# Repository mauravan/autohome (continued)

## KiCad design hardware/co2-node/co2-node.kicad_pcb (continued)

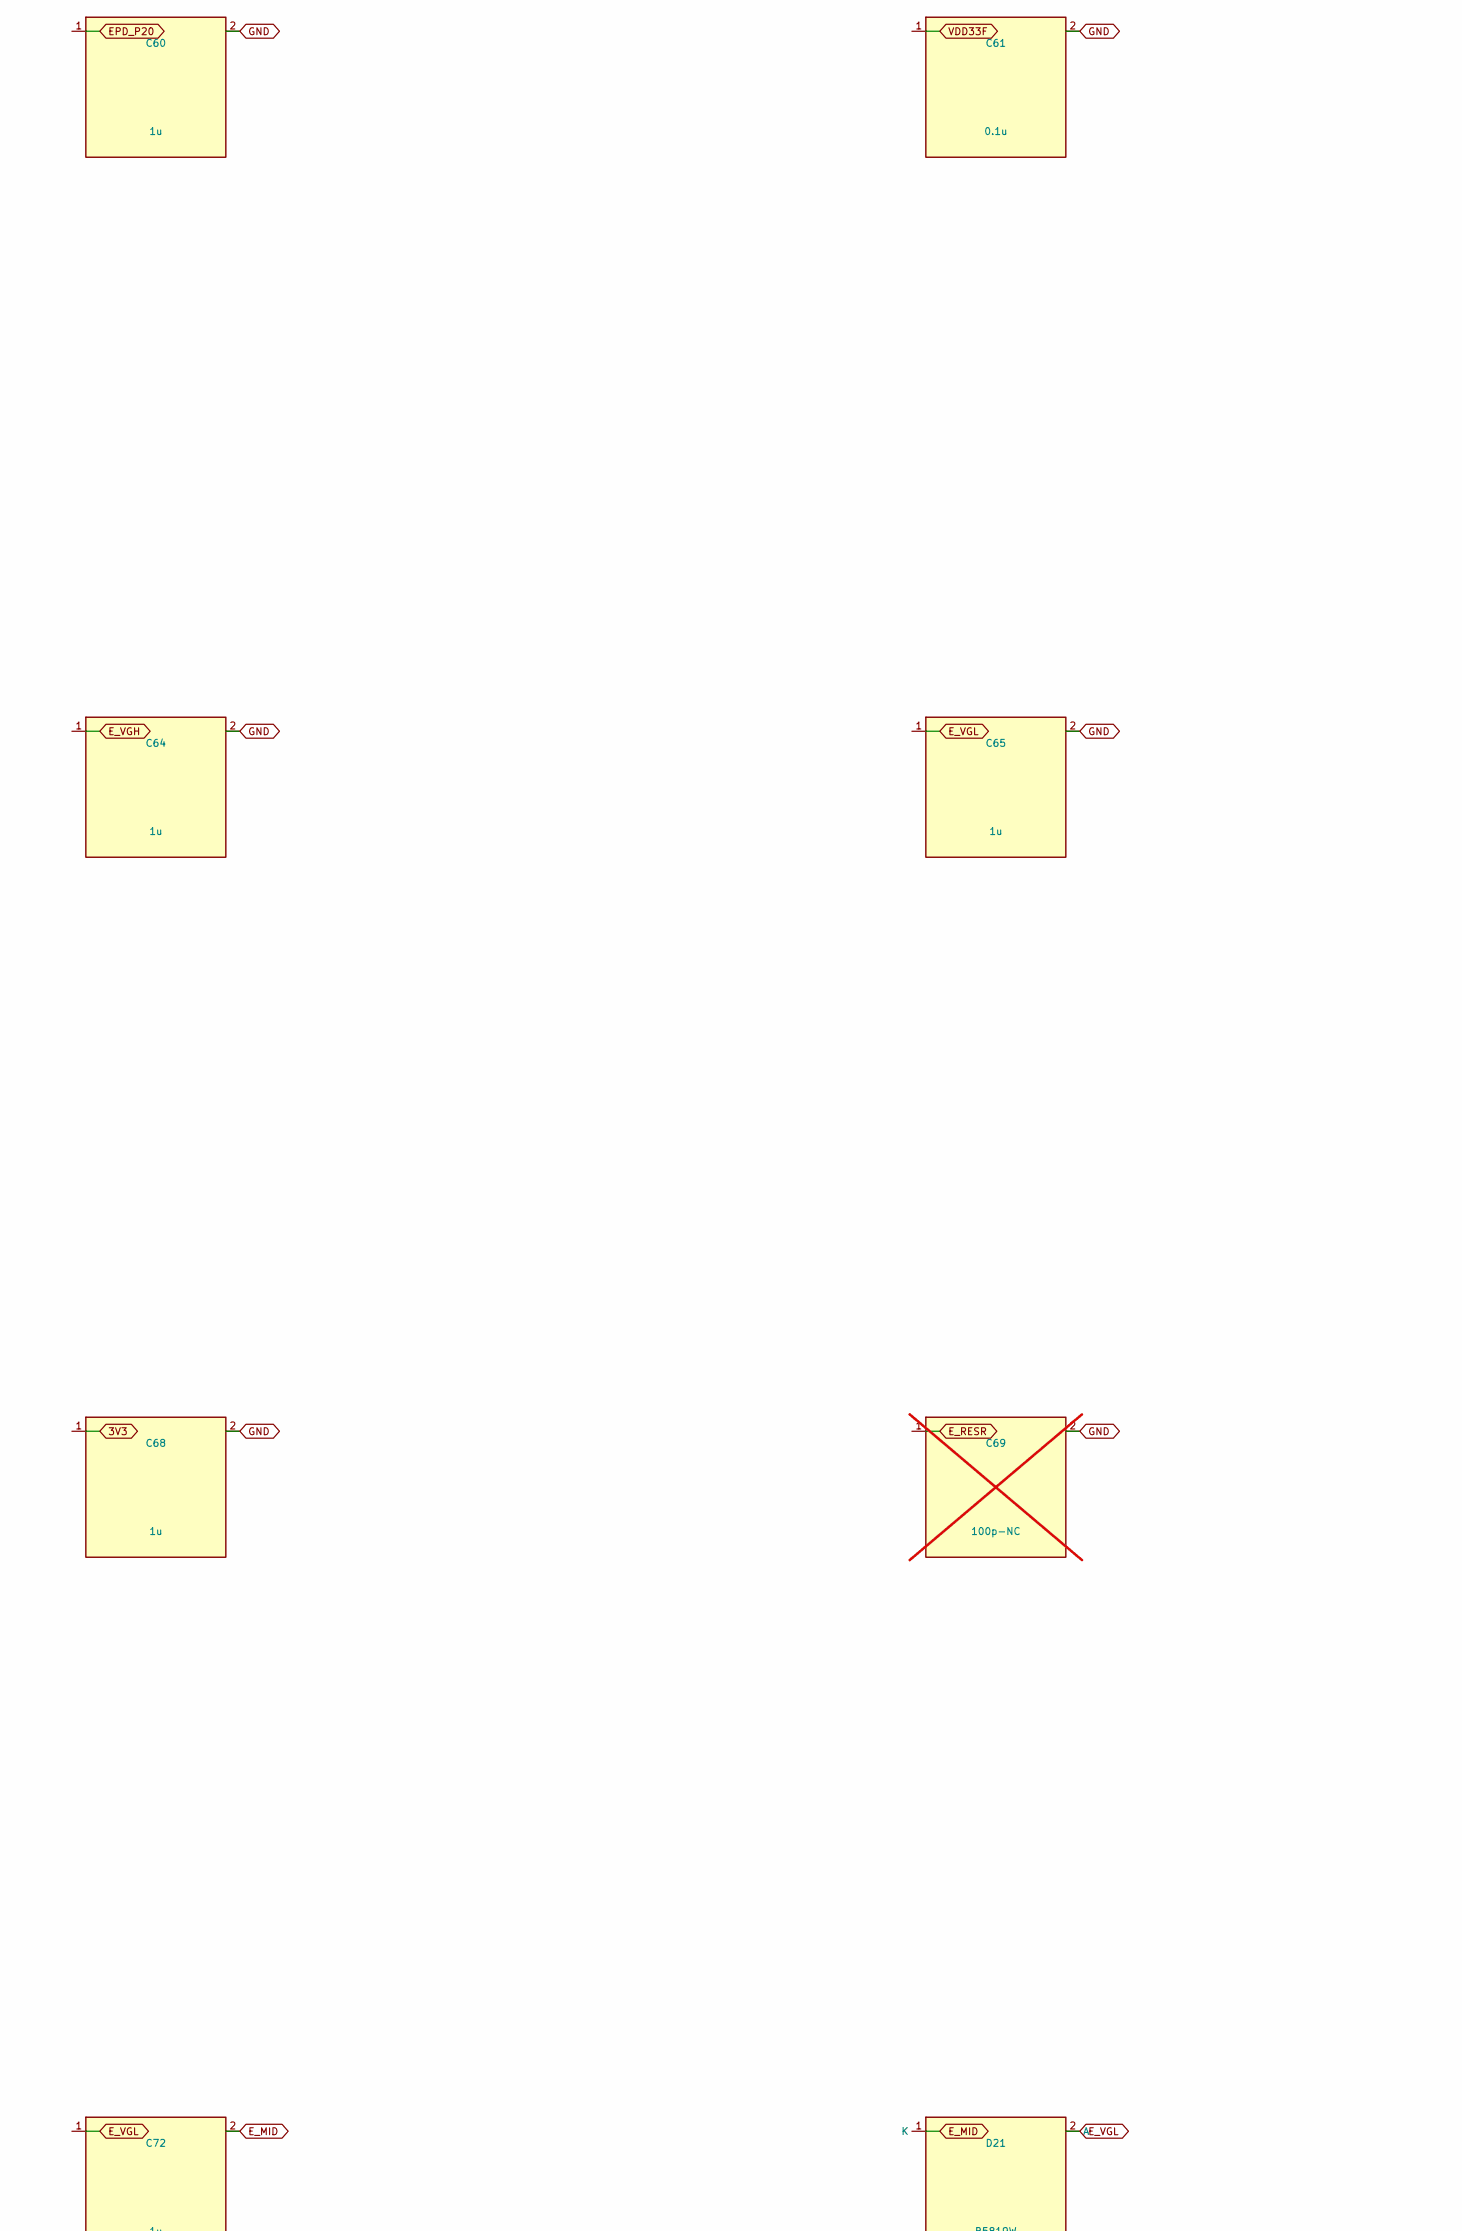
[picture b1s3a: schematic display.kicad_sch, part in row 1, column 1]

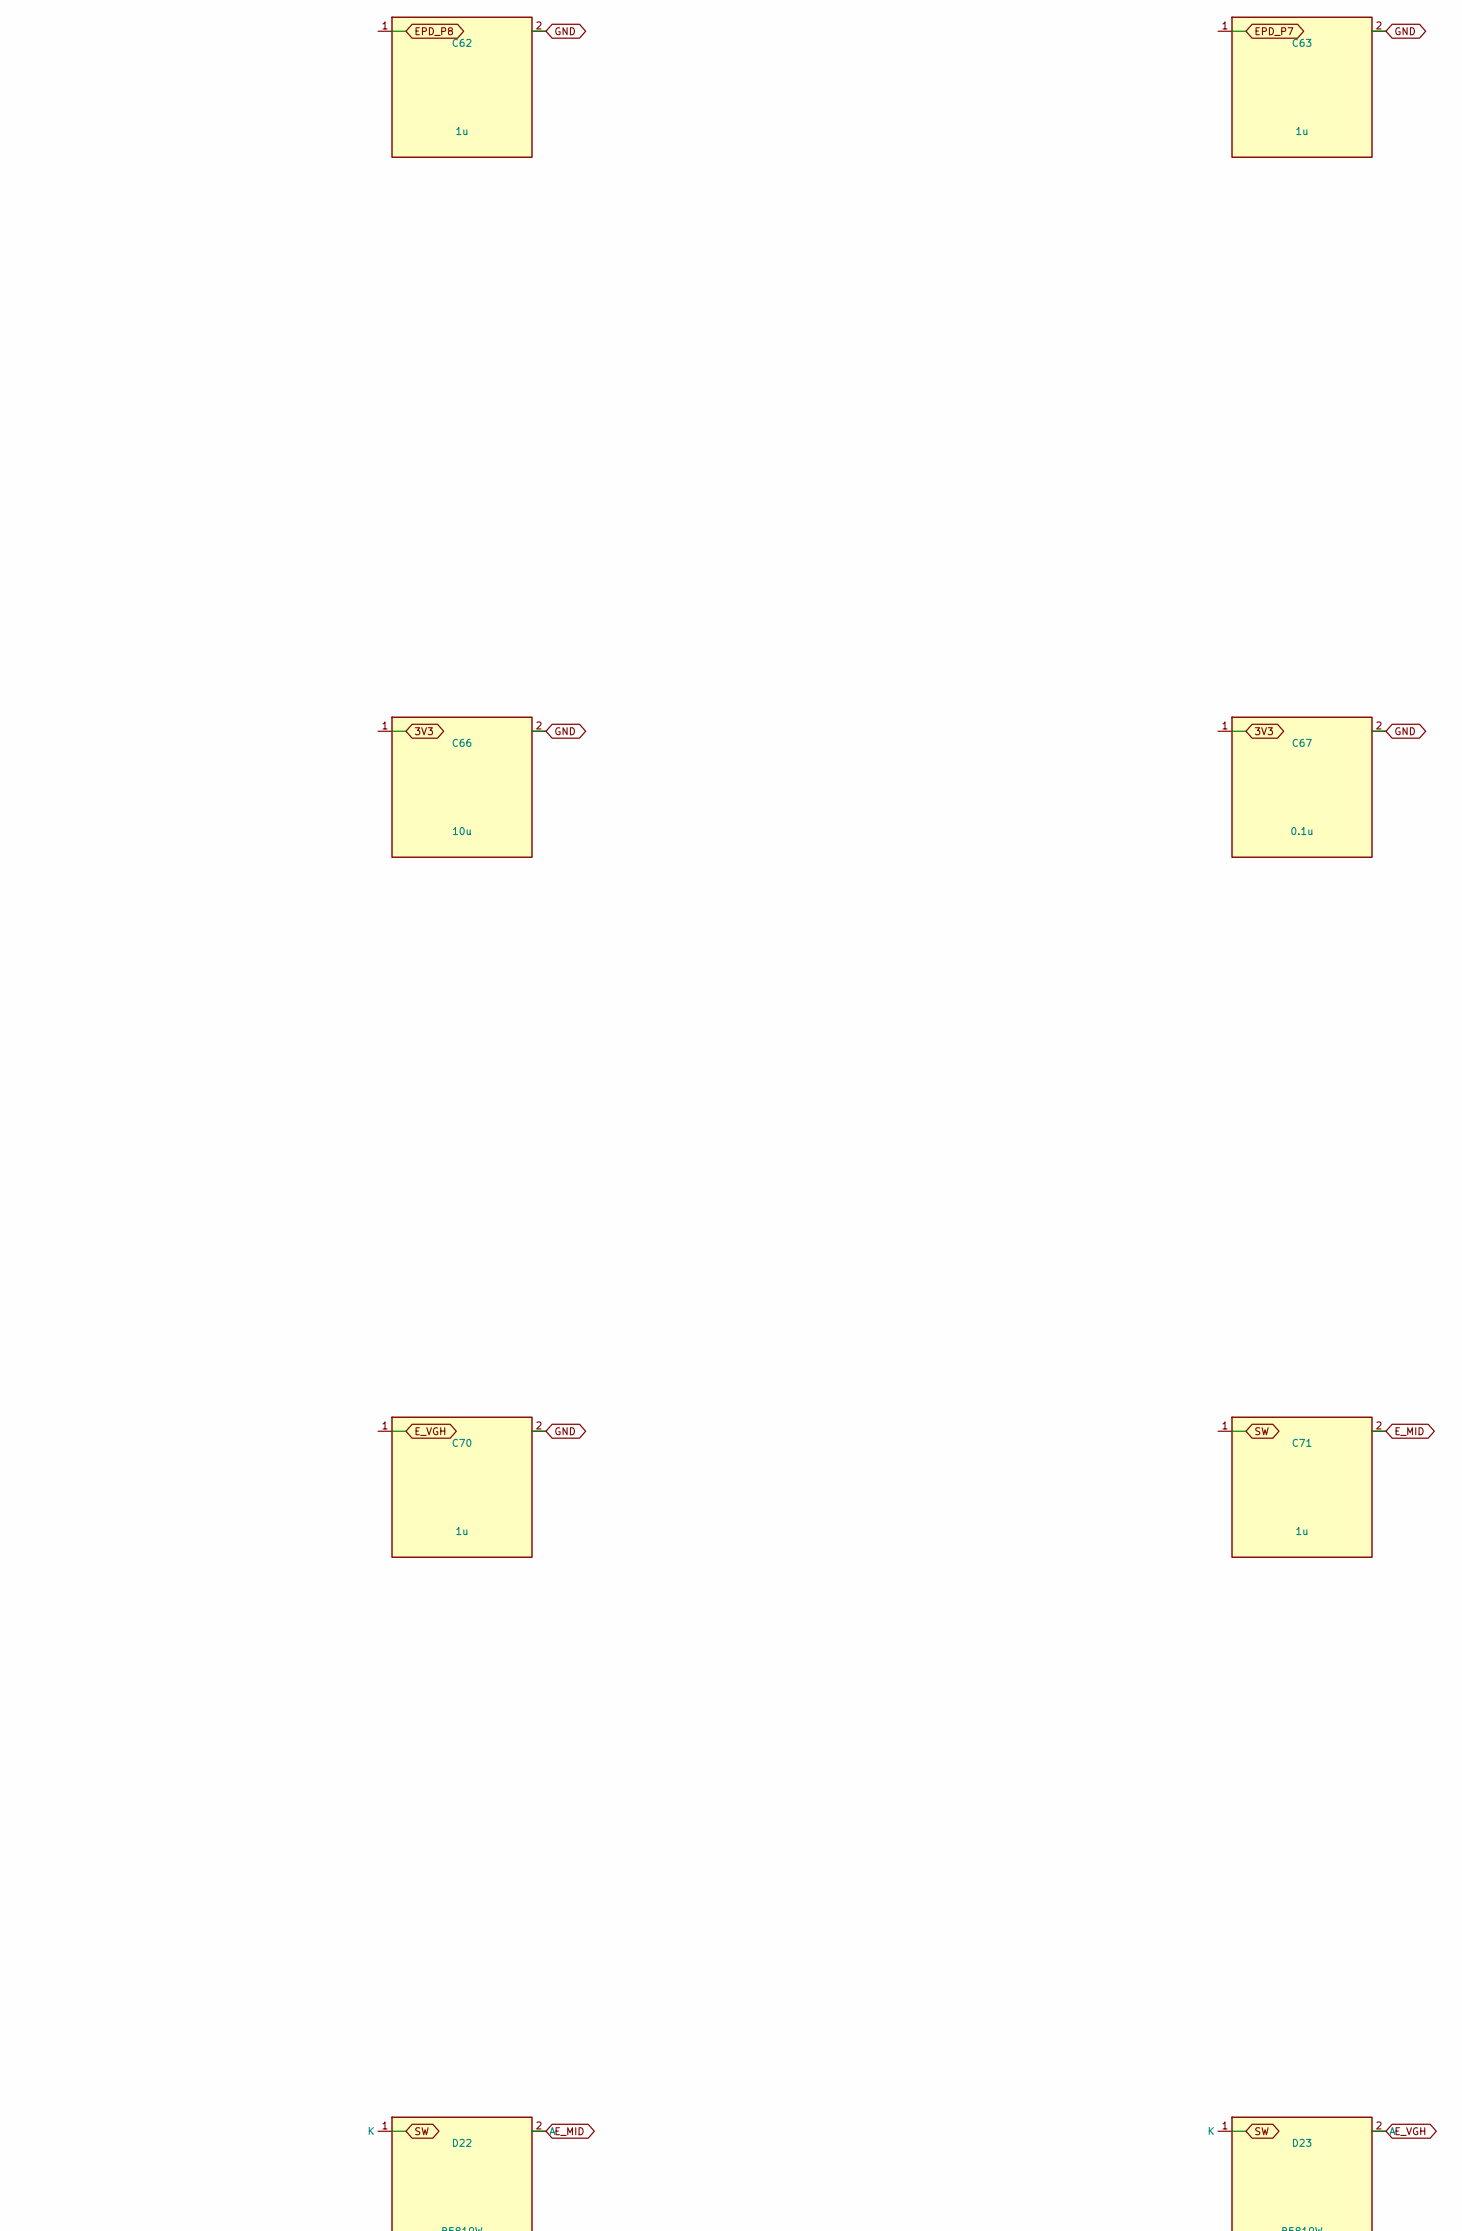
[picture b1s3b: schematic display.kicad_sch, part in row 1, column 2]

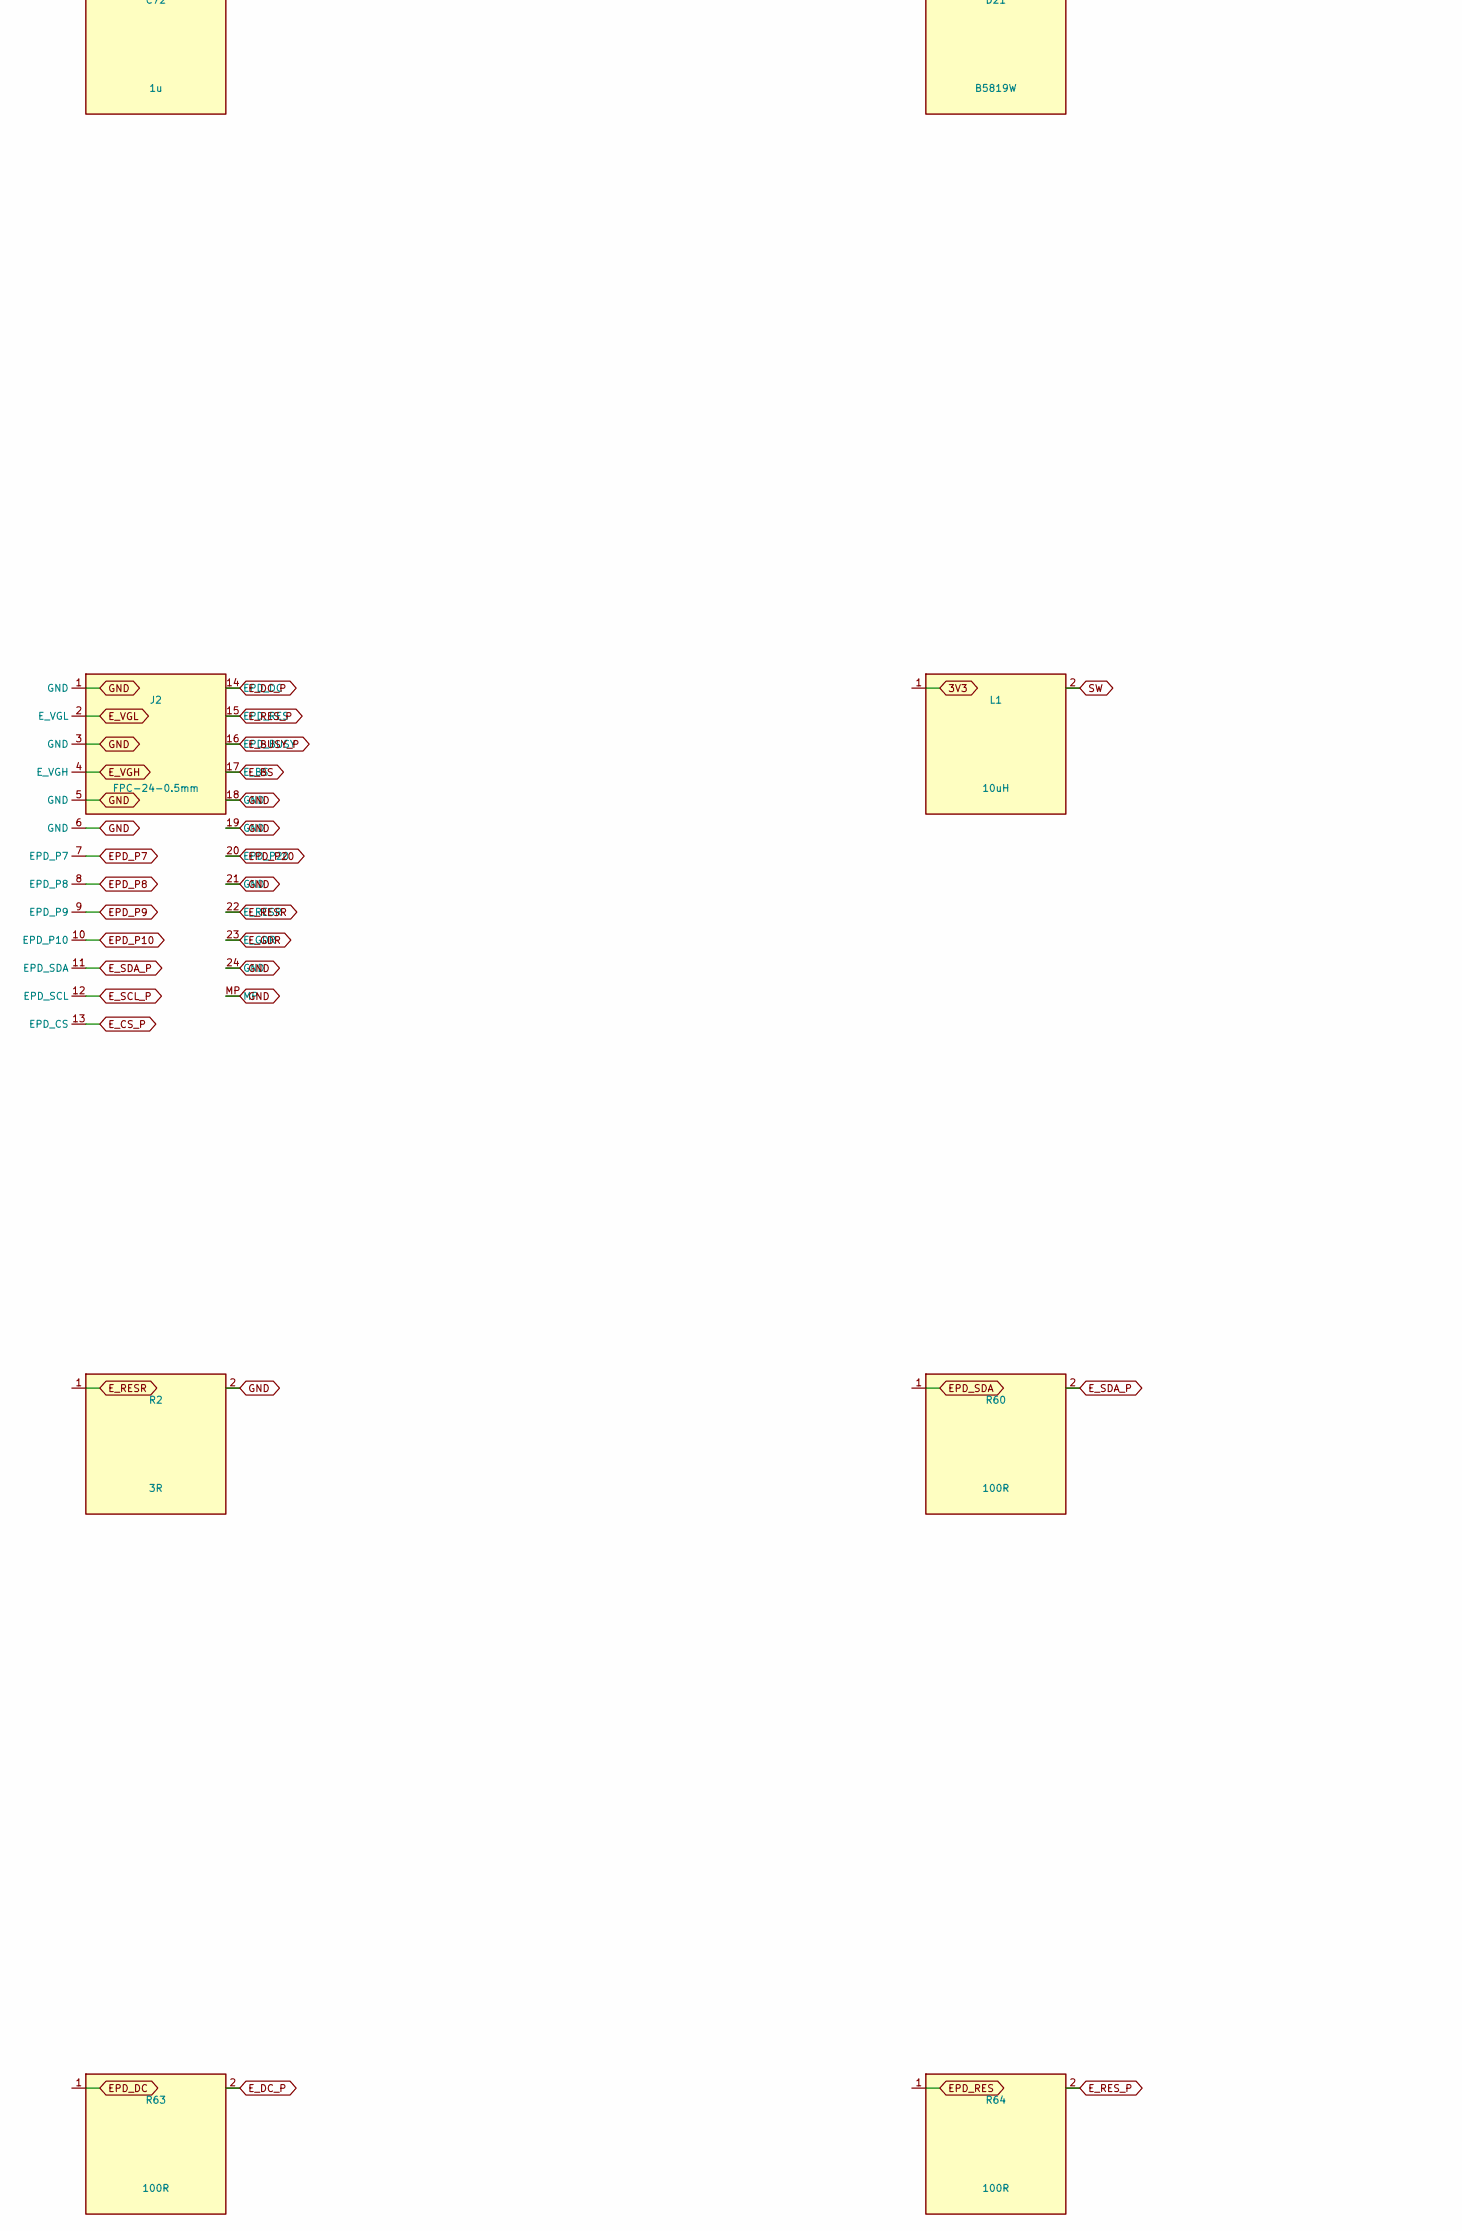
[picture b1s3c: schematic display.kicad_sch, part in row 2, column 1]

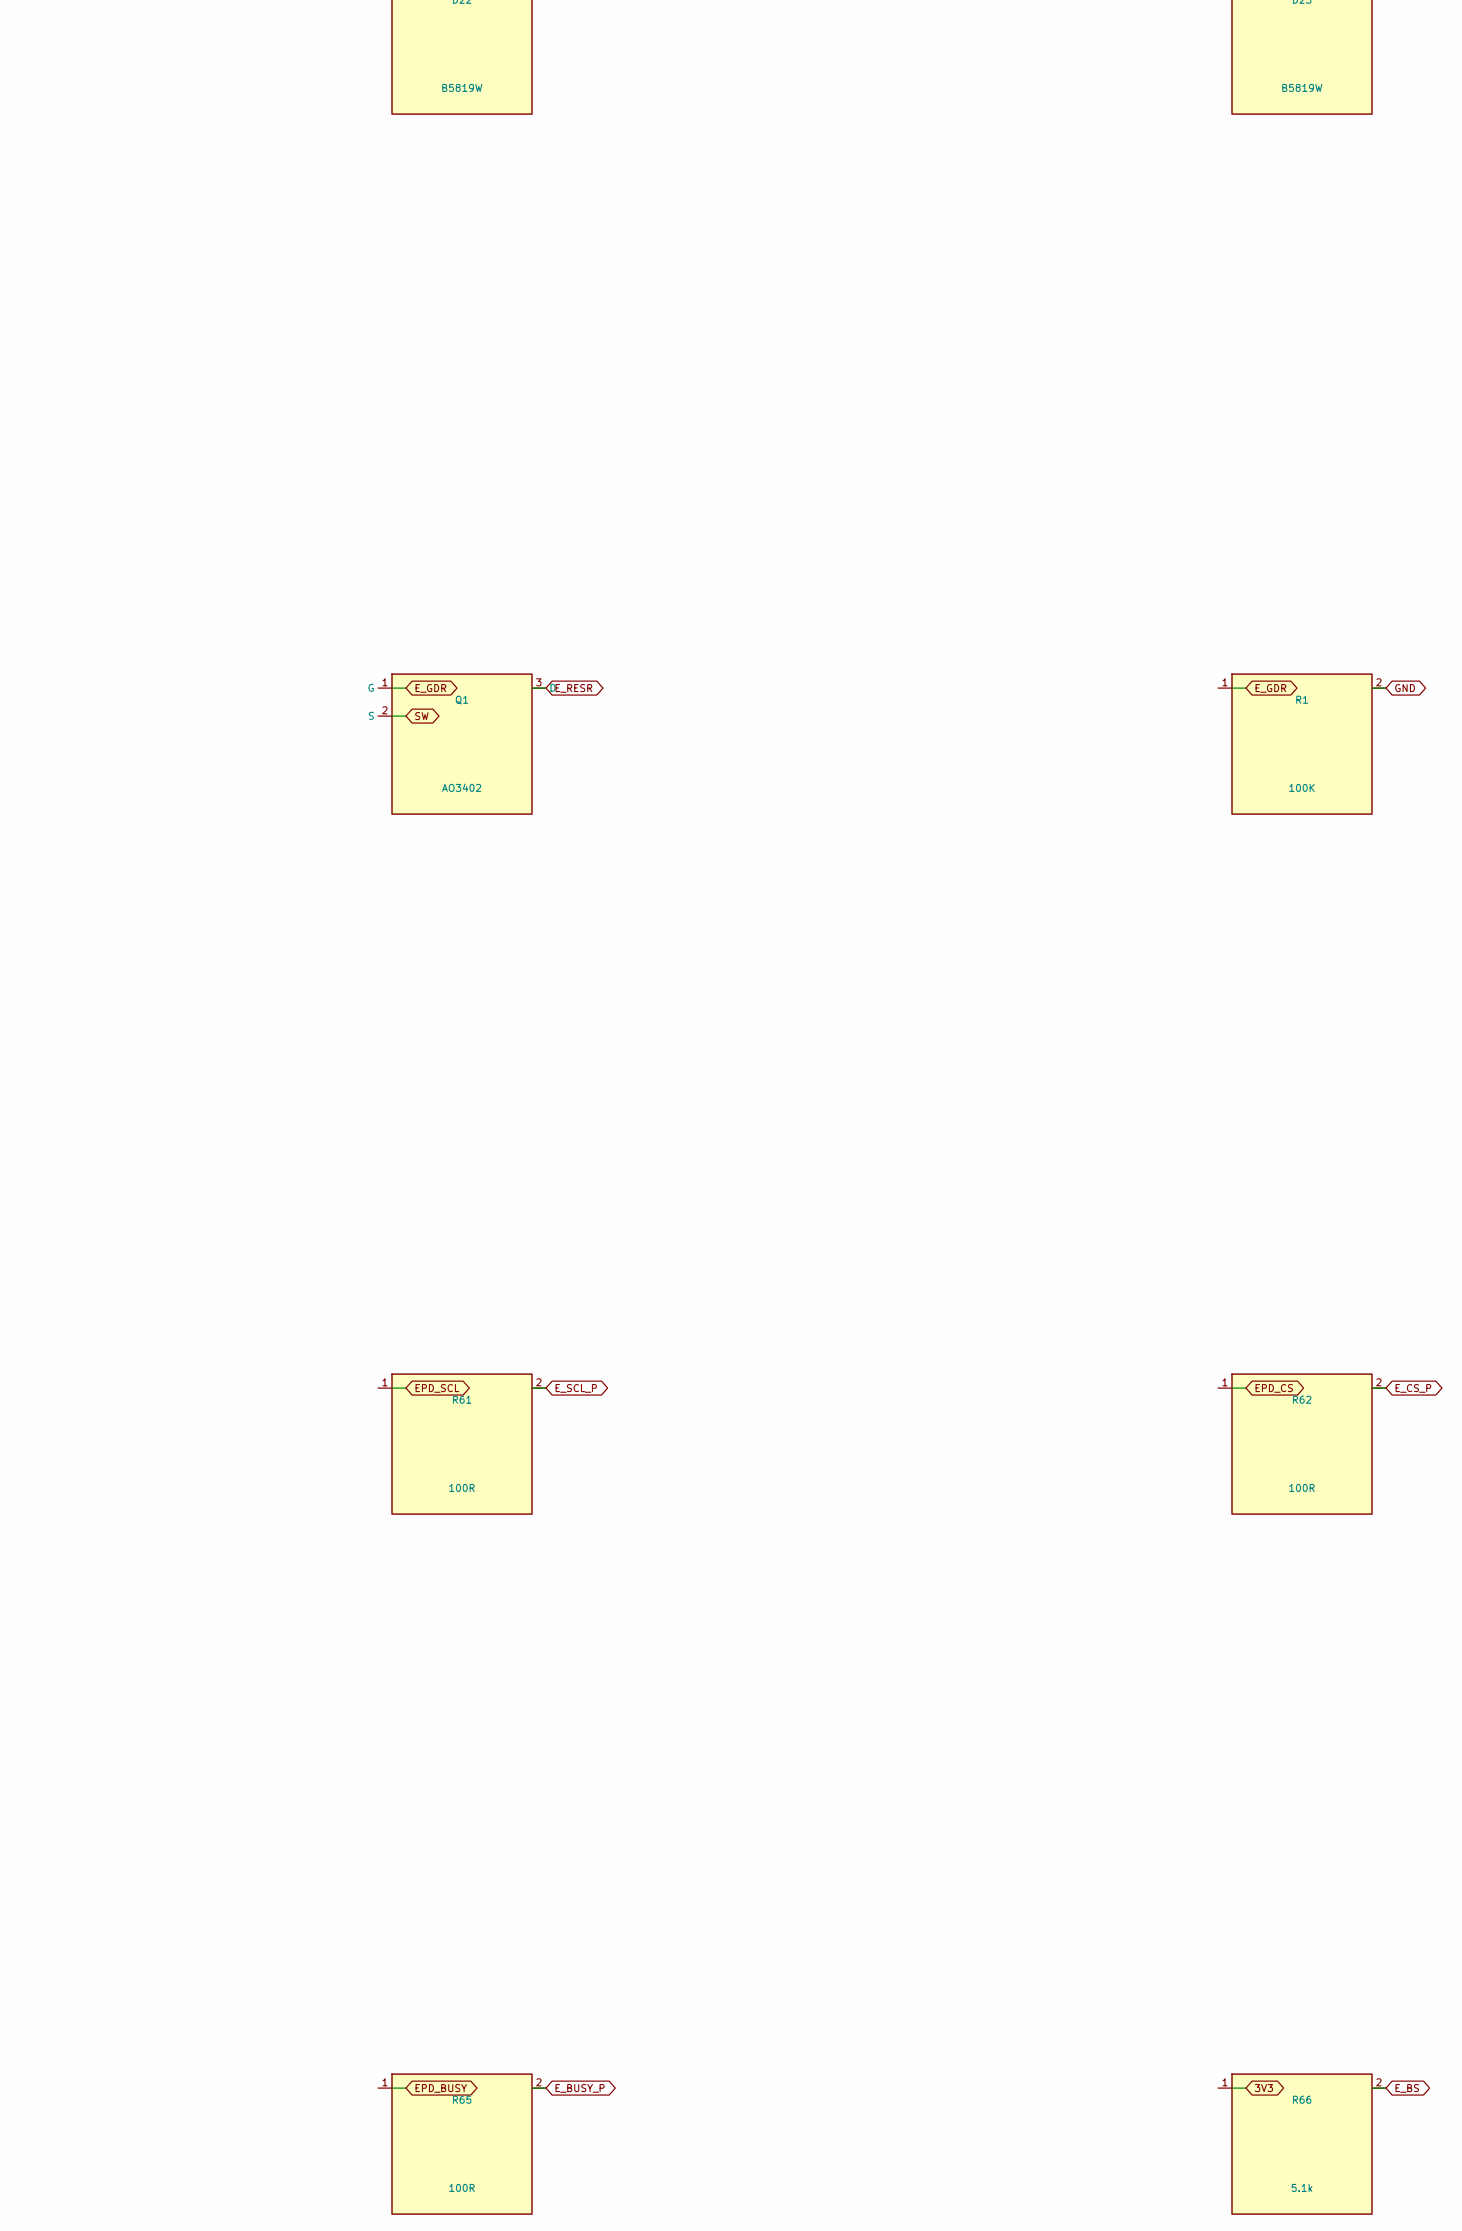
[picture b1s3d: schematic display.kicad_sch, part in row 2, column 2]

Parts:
C60, C62, C63, C64, C65, C68, C70, C71, C72: 1u; C_0402_1005Metric; MPN CL05B105KP5NNNC
C61, C67: 0.1u; C_0402_1005Metric; MPN CL05B104KP5NNNC
C66: 10u; C_0603_1608Metric; MPN CL10A106KP8NNNC
C69: 100p-NC; C_0402_1005Metric; not fitted
D21, D22, D23: B5819W; D_SOD-323; MPN B5819W
J2: FPC-24-0.5mm; Hirose_FH12-24S-0.5SH_1x24-1MP_P0.50mm_Horizontal; MPN FH12-24S-0.5SH
L1: 10uH; L_0603_1608Metric; MPN LQH3NPN100MJRL
Q1: AO3402; SOT-23; MPN AO3402
R1: 100K; R_0402_1005Metric; MPN RC0402-100K-1%
R2: 3R; R_0603_1608Metric; MPN RC0603-3R-1%
R60, R61, R62, R63, R64, R65: 100R; R_0402_1005Metric; MPN RC0402-100R-1%
R66: 5.1k; R_0402_1005Metric; MPN RC0402-5.1k-1%

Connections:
3V3: C66.1, C67.1, C68.1, L1.1, R66.1; also elsewhere on the board
EPD_BUSY: R65.1; also elsewhere on the board
EPD_CS: R62.1; also elsewhere on the board
EPD_DC: R63.1; also elsewhere on the board
EPD_P7: C63.1, J2.7 (EPD_P7)
EPD_P8: C62.1, J2.8 (EPD_P8)
EPD_P9: J2.9 (EPD_P9)
EPD_P10: J2.10 (EPD_P10)
EPD_P20: C60.1, J2.20 (EPD_P20)
EPD_RES: R64.1; also elsewhere on the board
EPD_SCL: R61.1; also elsewhere on the board
EPD_SDA: R60.1; also elsewhere on the board
E_BS: J2.17 (E_BS), R66.2
E_BUSY_P: J2.16 (EPD_BUSY), R65.2
E_CS_P: J2.13 (EPD_CS), R62.2
E_DC_P: J2.14 (EPD_DC), R63.2
E_GDR: J2.23 (E_GDR), Q1.1 (G), R1.1
E_MID: C71.2, C72.2, D21.1 (K), D22.2 (A)
E_RESR: C69.1, J2.22 (E_RESR), Q1.3 (D), R2.1
E_RES_P: J2.15 (EPD_RES), R64.2
E_SCL_P: J2.12 (EPD_SCL), R61.2
E_SDA_P: J2.11 (EPD_SDA), R60.2
E_VGH: C64.1, C70.1, D23.2 (A), J2.4 (E_VGH)
E_VGL: C65.1, C72.1, D21.2 (A), J2.2 (E_VGL)
GND: C60.2, C61.2, C62.2, C63.2, C64.2, C65.2, C66.2, C67.2, C68.2, C69.2, C70.2, J2.1 (GND), J2.3 (GND), J2.5 (GND), J2.6 (GND), J2.18 (GND), J2.19 (GND), J2.21 (GND), J2.24 (GND), J2.MP, R1.2, R2.2; also elsewhere on the board
SW: C71.1, D22.1 (K), D23.1 (K), L1.2, Q1.2 (S)
VDD33F: C61.1

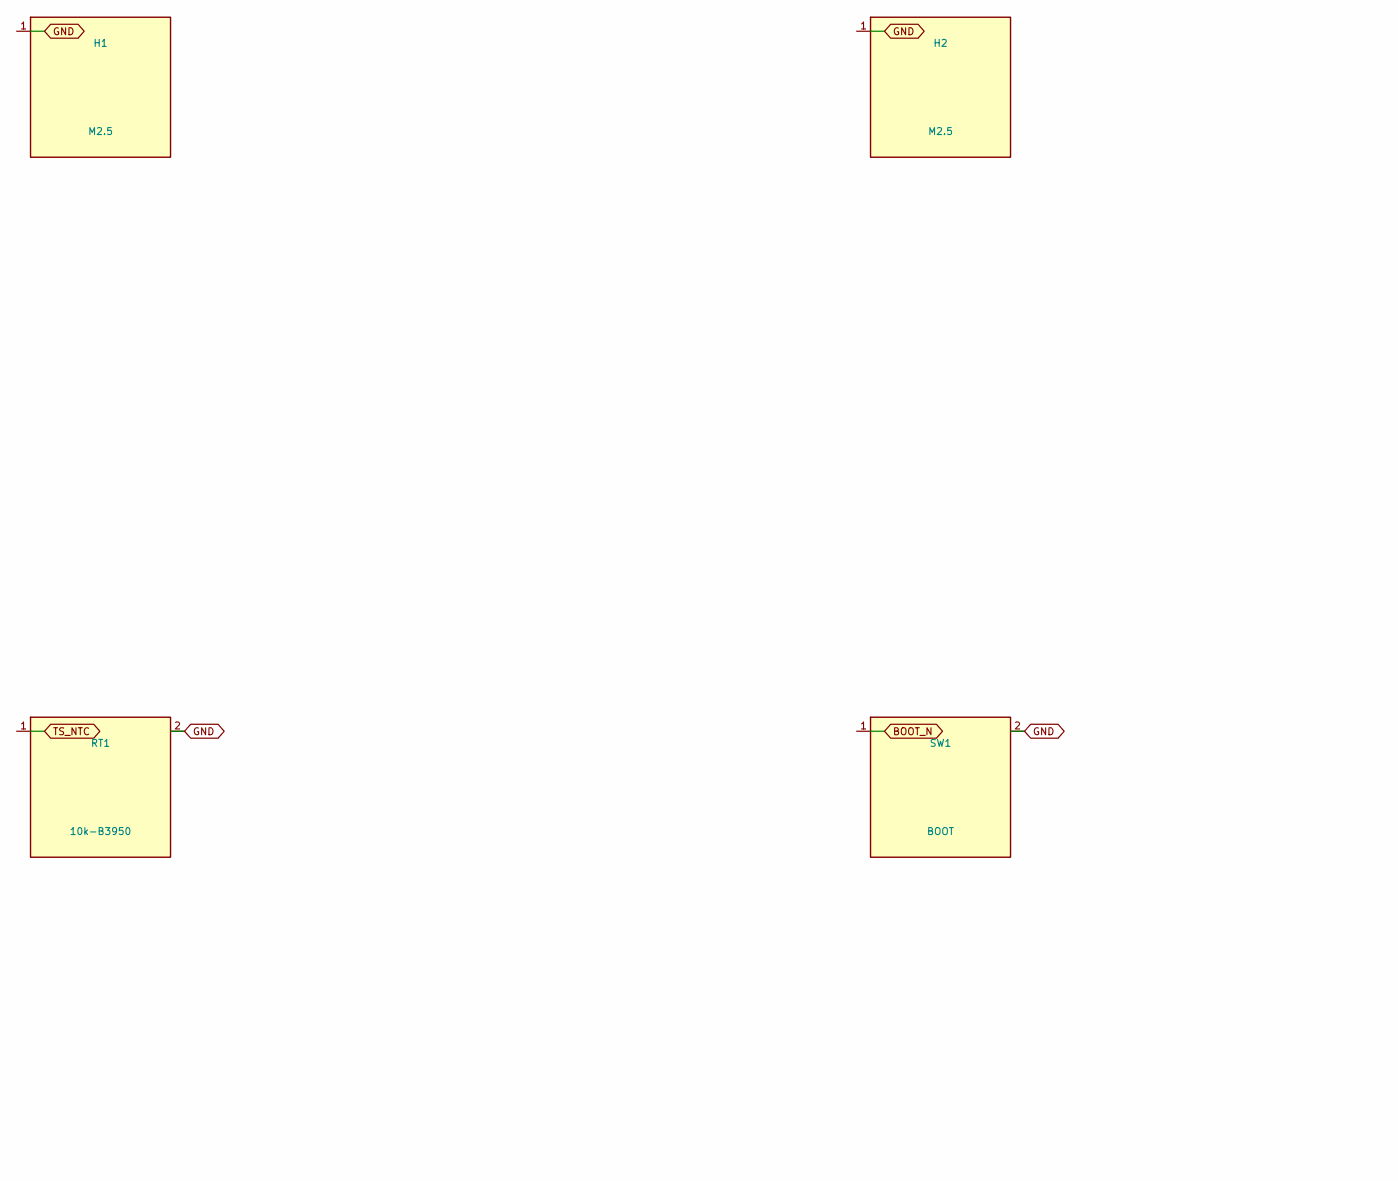
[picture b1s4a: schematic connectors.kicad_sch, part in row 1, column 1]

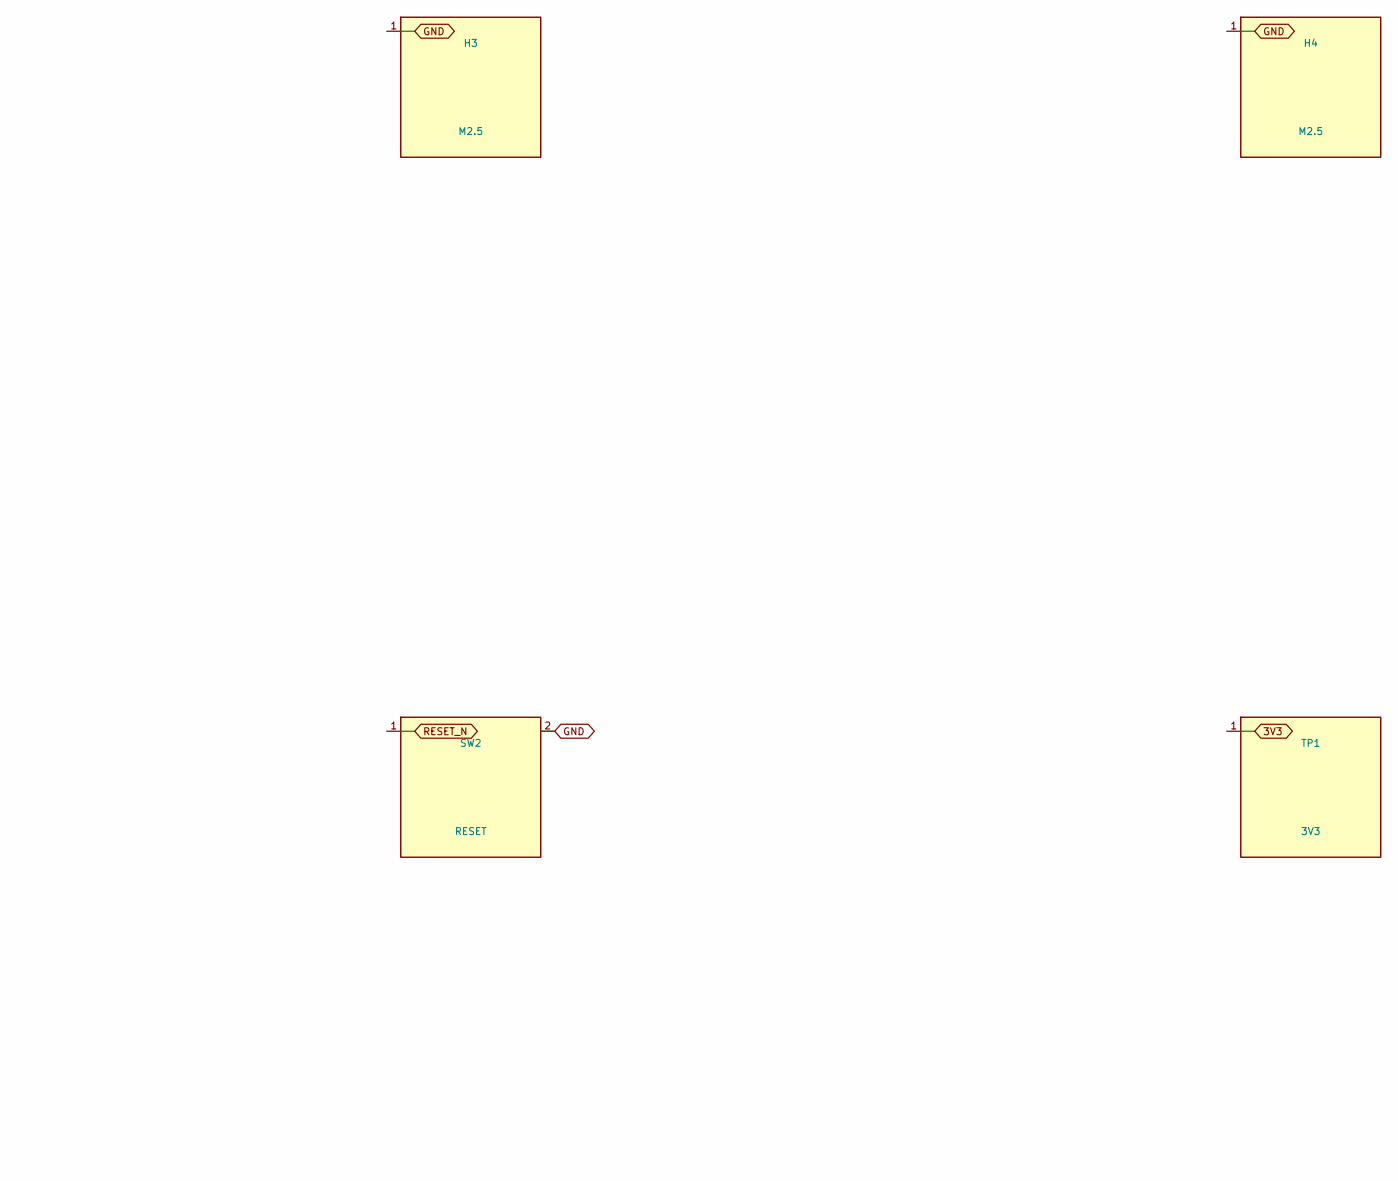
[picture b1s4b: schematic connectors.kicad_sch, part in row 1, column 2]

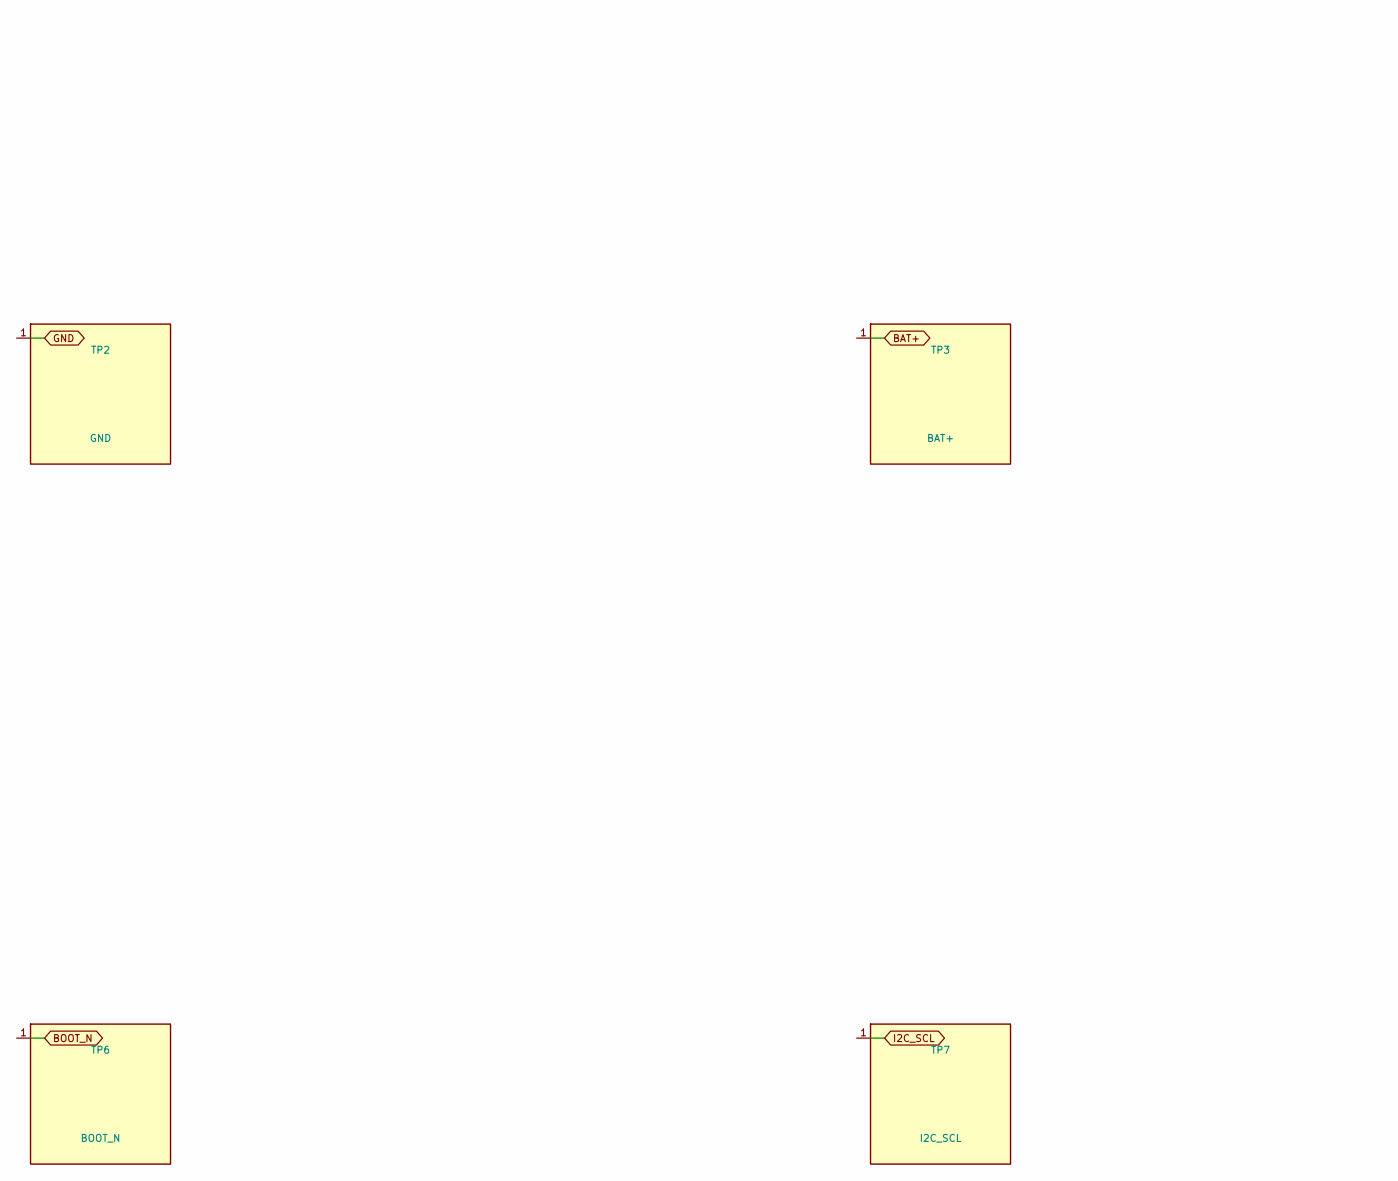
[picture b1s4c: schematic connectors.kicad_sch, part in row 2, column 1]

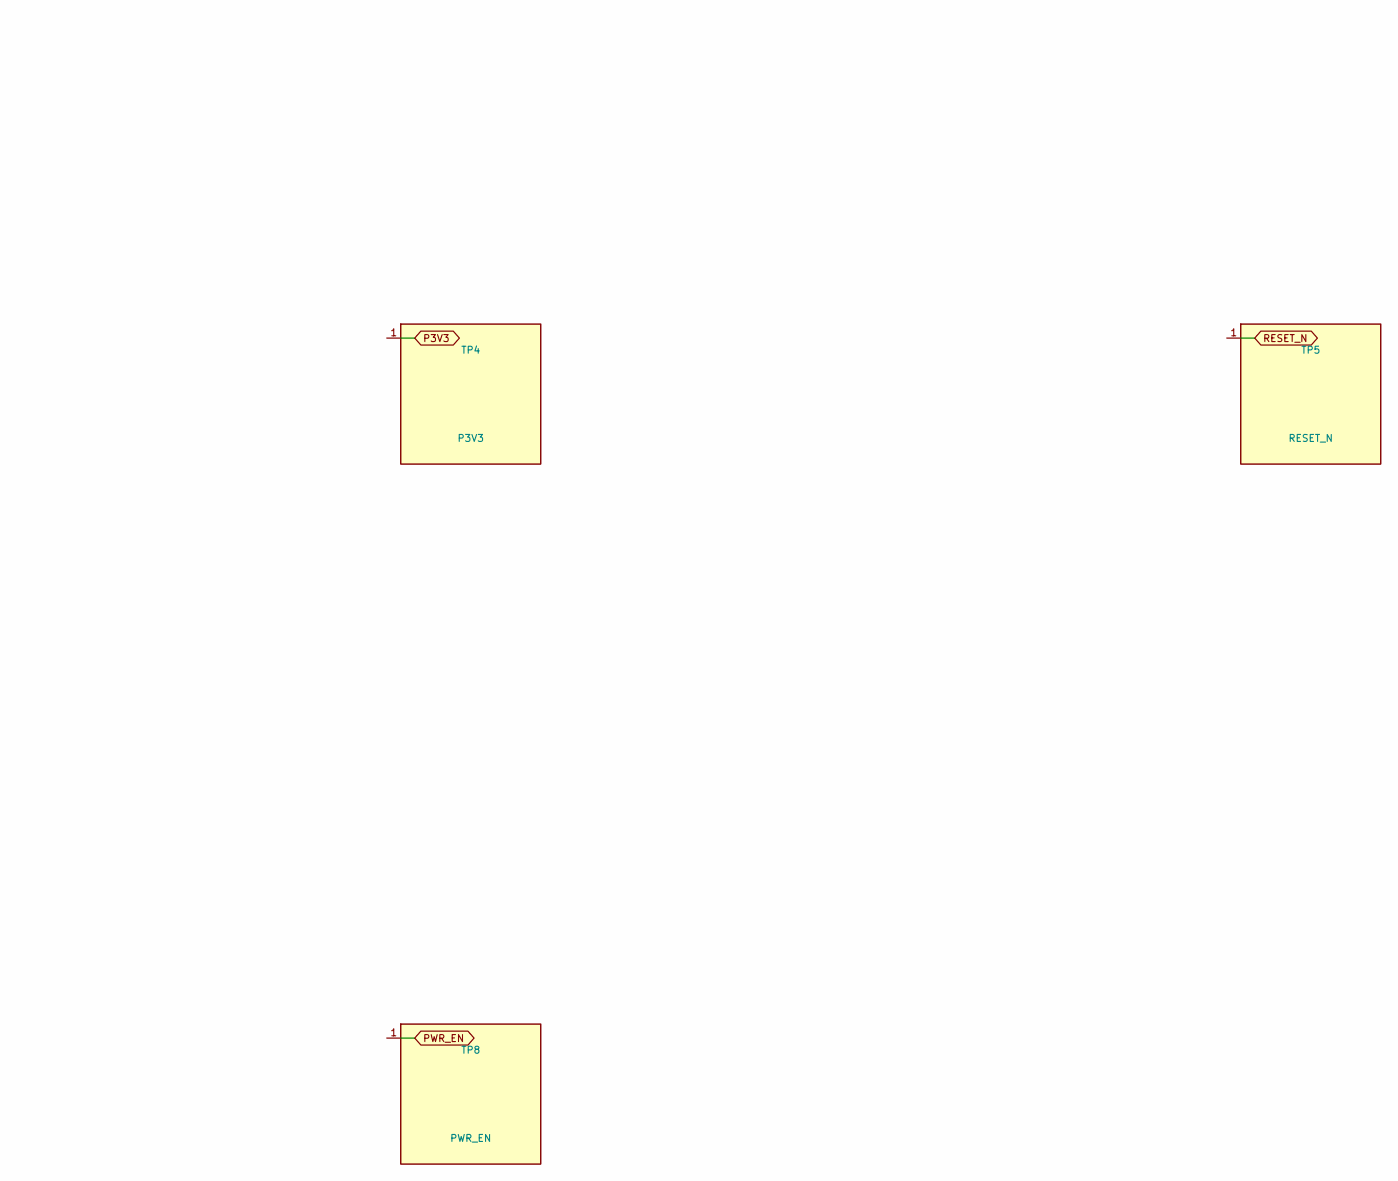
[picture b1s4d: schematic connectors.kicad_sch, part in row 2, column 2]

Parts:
H1, H2, H3, H4: M2.5; MountingHole_2.7mm_M2.5_Pad
RT1: 10k-B3950; R_0603_1608Metric; MPN NCP18XH103FDBRB
SW1: BOOT; SW_Push_1P1T_NO_CK_KMR2; MPN TL3305
SW2: RESET; SW_Push_1P1T_NO_CK_KMR2; MPN TL3305
TP1: 3V3; TestPoint_Pad_1.0x1.0mm
TP2: GND; TestPoint_Pad_1.0x1.0mm
TP3: BAT+; TestPoint_Pad_1.0x1.0mm
TP4: P3V3; TestPoint_Pad_1.0x1.0mm
TP5: RESET_N; TestPoint_Pad_1.0x1.0mm
TP6: BOOT_N; TestPoint_Pad_1.0x1.0mm
TP7: I2C_SCL; TestPoint_Pad_1.0x1.0mm
TP8: PWR_EN; TestPoint_Pad_1.0x1.0mm

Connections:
3V3: TP1.1; also elsewhere on the board
BAT+: TP3.1; also elsewhere on the board
BOOT_N: SW1.1, TP6.1; also elsewhere on the board
GND: H1.1, H2.1, H3.1, H4.1, RT1.2, SW1.2, SW2.2, TP2.1; also elsewhere on the board
I2C_SCL: TP7.1; also elsewhere on the board
P3V3: TP4.1; also elsewhere on the board
PWR_EN: TP8.1; also elsewhere on the board
RESET_N: SW2.1, TP5.1; also elsewhere on the board
TS_NTC: RT1.1; also elsewhere on the board

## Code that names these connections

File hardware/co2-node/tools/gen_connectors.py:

#!/usr/bin/env python3
"""Connectors sheet: holder, NTC, buttons, test pads, mounting, label ref.

BT1/NTC live on power sheet as electrical parts; this sheet carries the
mechanical holder symbol + NTC placement note + BOOT/RESET buttons +
8 test pads (3V3 GND BAT P3V3 EN GPIO9 SCL PWR_EN) + mounting holes.
"""
import sys; sys.path.insert(0, __import__("pathlib").Path(__file__).resolve().parent.__str__())
from gen_common import *


def build_connectors():
    L = [sheet_head(f"CO2 node rev {REV} - {SHEETS['connectors'][1]}")]
    cx = 30.0
    # holder mechanical (electrical BT1 on power sheet shown as linked ref)
    L += [lbl("CELL+", cx - 12, 40)]
    L += [txt("BT1 holder electrical part is on the power sheet.", cx - 12, 34),
          txt("Placement: back side, top edge y=15mm.", cx - 12, 48)]
    # NTC adjacent to cell -> TS net (electrical on power sheet TS pin)
    L += [sym("Device:R_NTC", "RT1", "10k-B3950", "co2-node:R_0603",
              cx + 25, 40, [("1", "TS_NTC"), ("2", "GND")],
              "NTC at cell; BQ24074 TS: 75uA bias")]
    L += [lbl("TS_NTC", cx + 25, 34)]
    # BOOT / RESET tactile buttons to GND
    L += [sym("co2-node:SW_TACT", "SW1", "BOOT", "co2-node:SW-3x4",
              cx + 50, 35, [("1", "BOOT_N"), ("2", "GND")],
              "BOOT pinhole in case")]
    L += [sym("co2-node:SW_TACT", "SW2", "RESET", "co2-node:SW-3x4",
              cx + 50, 50, [("1", "RESET_N"), ("2", "GND")],
              "RESET pinhole in case")]
    L += [lbl("BOOT_N", cx + 42, 35), lbl("RESET_N", cx + 42, 50)]
    # charge LED is D20 on power sheet; light-pipe note
    # test pads 1.0mm: 3V3 GND BAT P3V3 EN GPIO9 SCL PWR_EN
    pads = [("TP1", "3V3"), ("TP2", "GND"), ("TP3", "BAT+"),
            ("TP4", "P3V3"), ("TP5", "RESET_N"), ("TP6", "BOOT_N"),
            ("TP7", "I2C_SCL"), ("TP8", "PWR_EN")]
    # NOTE: plan says EN + GPIO9; RESET_N == EN net, BOOT_N == GPIO9 net.
    for i, (ref, net) in enumerate(pads):
        L += [sym("co2-node:TESTPAD", ref, net, "co2-node:TP-1.0mm",
                  cx + 75 + (i % 4) * 12, 32 + (i // 4) * 12,
                  [("1", net)], f"pogo 1.0mm; front/bottom clear of holder")]
        L += [lbl(net, cx + 75 + (i % 4) * 12, 26 + (i // 4) * 12)]
    # mounting holes + label ref
    for i, (ref, mx_, my_) in enumerate(
            [("H1", 3.5, 3.5), ("H2", 91.5, 3.5),
             ("H3", 3.5, 41.5), ("H4", 91.5, 41.5)]):
        L += [sym("co2-node:MOUNT_M2.5", ref, "M2.5",
                  "co2-node:MOUNT-2.5", cx + 110 + (i % 2) * 12,
                  30 + (i // 2) * 12, [("1", "GND")],
                  f"board hole ({mx_},{my_}mm); standoff")]
    L += [sym("co2-node:LABEL", "LBL1", "AH-CO2-1",
              "co2-node:LABEL-70x30", cx + 110, 60, [],
              "70x30 back label; no metal over antenna")]
    L += [gnd(cx + 25, 48), gnd(cx + 50, 42)]
    return L


def main():
    out = build_connectors()
    (HERE / "connectors.kicad_sch").write_text("\n".join(out) + "\n)\n")
    print(f"connectors: {len(chr(10).join(out))} bytes")


if __name__ == "__main__":
    main()
